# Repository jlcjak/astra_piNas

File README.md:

# Astra piNas — CM5 dual NVMe carrier

This project was an experiment in using GPT-6 Astra to create a complete PCB from a single initial prompt, followed by a request to fully route it.

**Initial prompt** *(lightly edited for spelling and grammar)*

> I need a new KiCad project with schematics for a small Raspberry Pi CM5 carrier board. It needs to take two full-size M.2 SSDs, so you will need a PCIe switch. Find parts for everything, along with symbols and footprints.
>
> It also needs one RJ45 Ethernet connector, an SD card slot, a barrel jack that accepts 9–25 V, PoE capability, and a power-only USB-C port. A second USB-C port should be used just for USB-to-UART.
>
> Find good symbols and footprints for everything, and keep it nice. Pay particular attention to the CM5 footprint and make sure it is correct. You have TI_API_KEY, TI_API_SECRET, MOUSER_API_KEY, DIGIKEY_CLIENT_ID and DIGIKEY_CLIENT_SECRET set as environment variables in `~/.local/share/codex`. You also have easyeda2kicad installed. You can use the other APIs for datasheets and create your own footprints too.
>
> Remember to put the footprints and symbols in self-contained project libraries. All parts should be well in stock and have a MANUFACTURER PART NUMBER property. Actually, let's use only in-stock LCSC parts, with 0402 as the minimum component size. Try to minimize the component count and number of passives.
>
> Place things logically on the board afterward so it is easy for me to route. Explicitly: do not look for other work on this computer that might help. It will not help and must not be used. Strictly.

**Routing follow-up** *(lightly edited for spelling and grammar)*

> OK, now fully route it. Feel free to move things around as much as you like; I like the current size. Make it nice and clean, and pick the stackup and everything. Use six layers at most. I think six makes sense here, actually.

Open **[astra_piNas.kicad_pro](astra_piNas.kicad_pro)** in **KiCad 10**. The project contains nine schematic sheets and a fully routed **100 × 120 mm, six-layer** board. Both 2280 NVMe sockets are on the underside. Use a **CM5 Lite** for the native microSD interface.

- [Routing and placement notes](docs/ROUTING.md), [selected stackup](docs/STACKUP.md)
- [Schematic PDF](docs/schematics.pdf)
- [Top copper view](docs/routing_top.svg), [bottom copper view](docs/routing_bottom.svg)
- [Top assembly view](docs/placement_top.svg), [bottom assembly view](docs/placement_bottom.svg)
- [BOM with MPNs and LCSC stock snapshots](docs/BOM.csv), [library provenance](docs/LIBRARIES.md)
- [Final validation summary](docs/routing_validation.json), [pair measurements](docs/pair_lengths.csv)
- [ERC](docs/erc.rpt), [PCB DRC](docs/drc.rpt), [schematic parity](docs/schematic_parity.rpt)

All symbols and footprints resolve through the project-local library tables to `lib/`. Available 3D models use project-relative paths. No unrelated local project was searched or reused; the Raspberry Pi reference files were downloaded from the official archive linked in [library provenance](docs/LIBRARIES.md).

The main project files above are the current design. Local routing experiments, tool caches and the downloaded CM5IO reference archive are excluded from this repository. Final routing measurements and validation reports are included under `docs/`. Regeneration scripts can overwrite manual edits. No fabrication package is released while the PoE hold remains unresolved.

**Board views**

Slightly angled 3D views of both sides, with project-local passive models:

Top and bottom placement views:

| Top | Bottom |
| --- | --- |
|  |  |

All six copper layers, viewed from the top in stackup order:

Individual layers are shown below. Click a layer name for the full-resolution vector drawing.

| Layer | Copper view |
| --- | --- |
| [L1 · F.Cu — outer routing](docs/images/astra_piNas-F_Cu.svg) |  |
| [L2 · In1.Cu — ground reference](docs/images/astra_piNas-In1_Cu.svg) |  |
| [L3 · In2.Cu — power and slow signals](docs/images/astra_piNas-In2_Cu.svg) |  |
| [L4 · In3.Cu — power and slow signals](docs/images/astra_piNas-In3_Cu.svg) |  |
| [L5 · In4.Cu — ground reference](docs/images/astra_piNas-In4_Cu.svg) |  |
| [L6 · B.Cu — outer routing](docs/images/astra_piNas-B_Cu.svg) |  |

**Schematic overview**

All nine sheets are shown below. Open the [schematic PDF](docs/schematics.pdf) to zoom into individual circuits.

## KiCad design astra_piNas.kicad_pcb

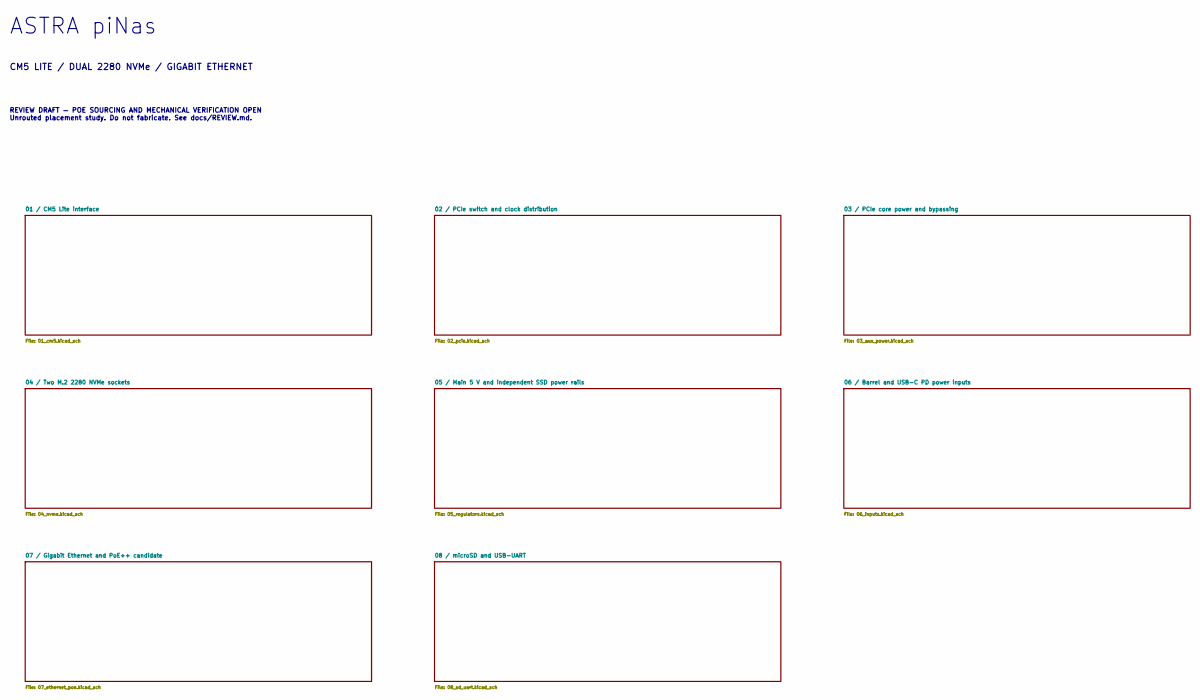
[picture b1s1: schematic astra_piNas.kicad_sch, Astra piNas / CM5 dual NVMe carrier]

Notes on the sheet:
ASTRA piNas
CM5 LITE / DUAL 2280 NVMe / GIGABIT ETHERNET
REVIEW DRAFT — POE SOURCING AND MECHANICAL VERIFICATION OPEN Unrouted placement study. Do not fabricate. See docs/REVIEW.md.

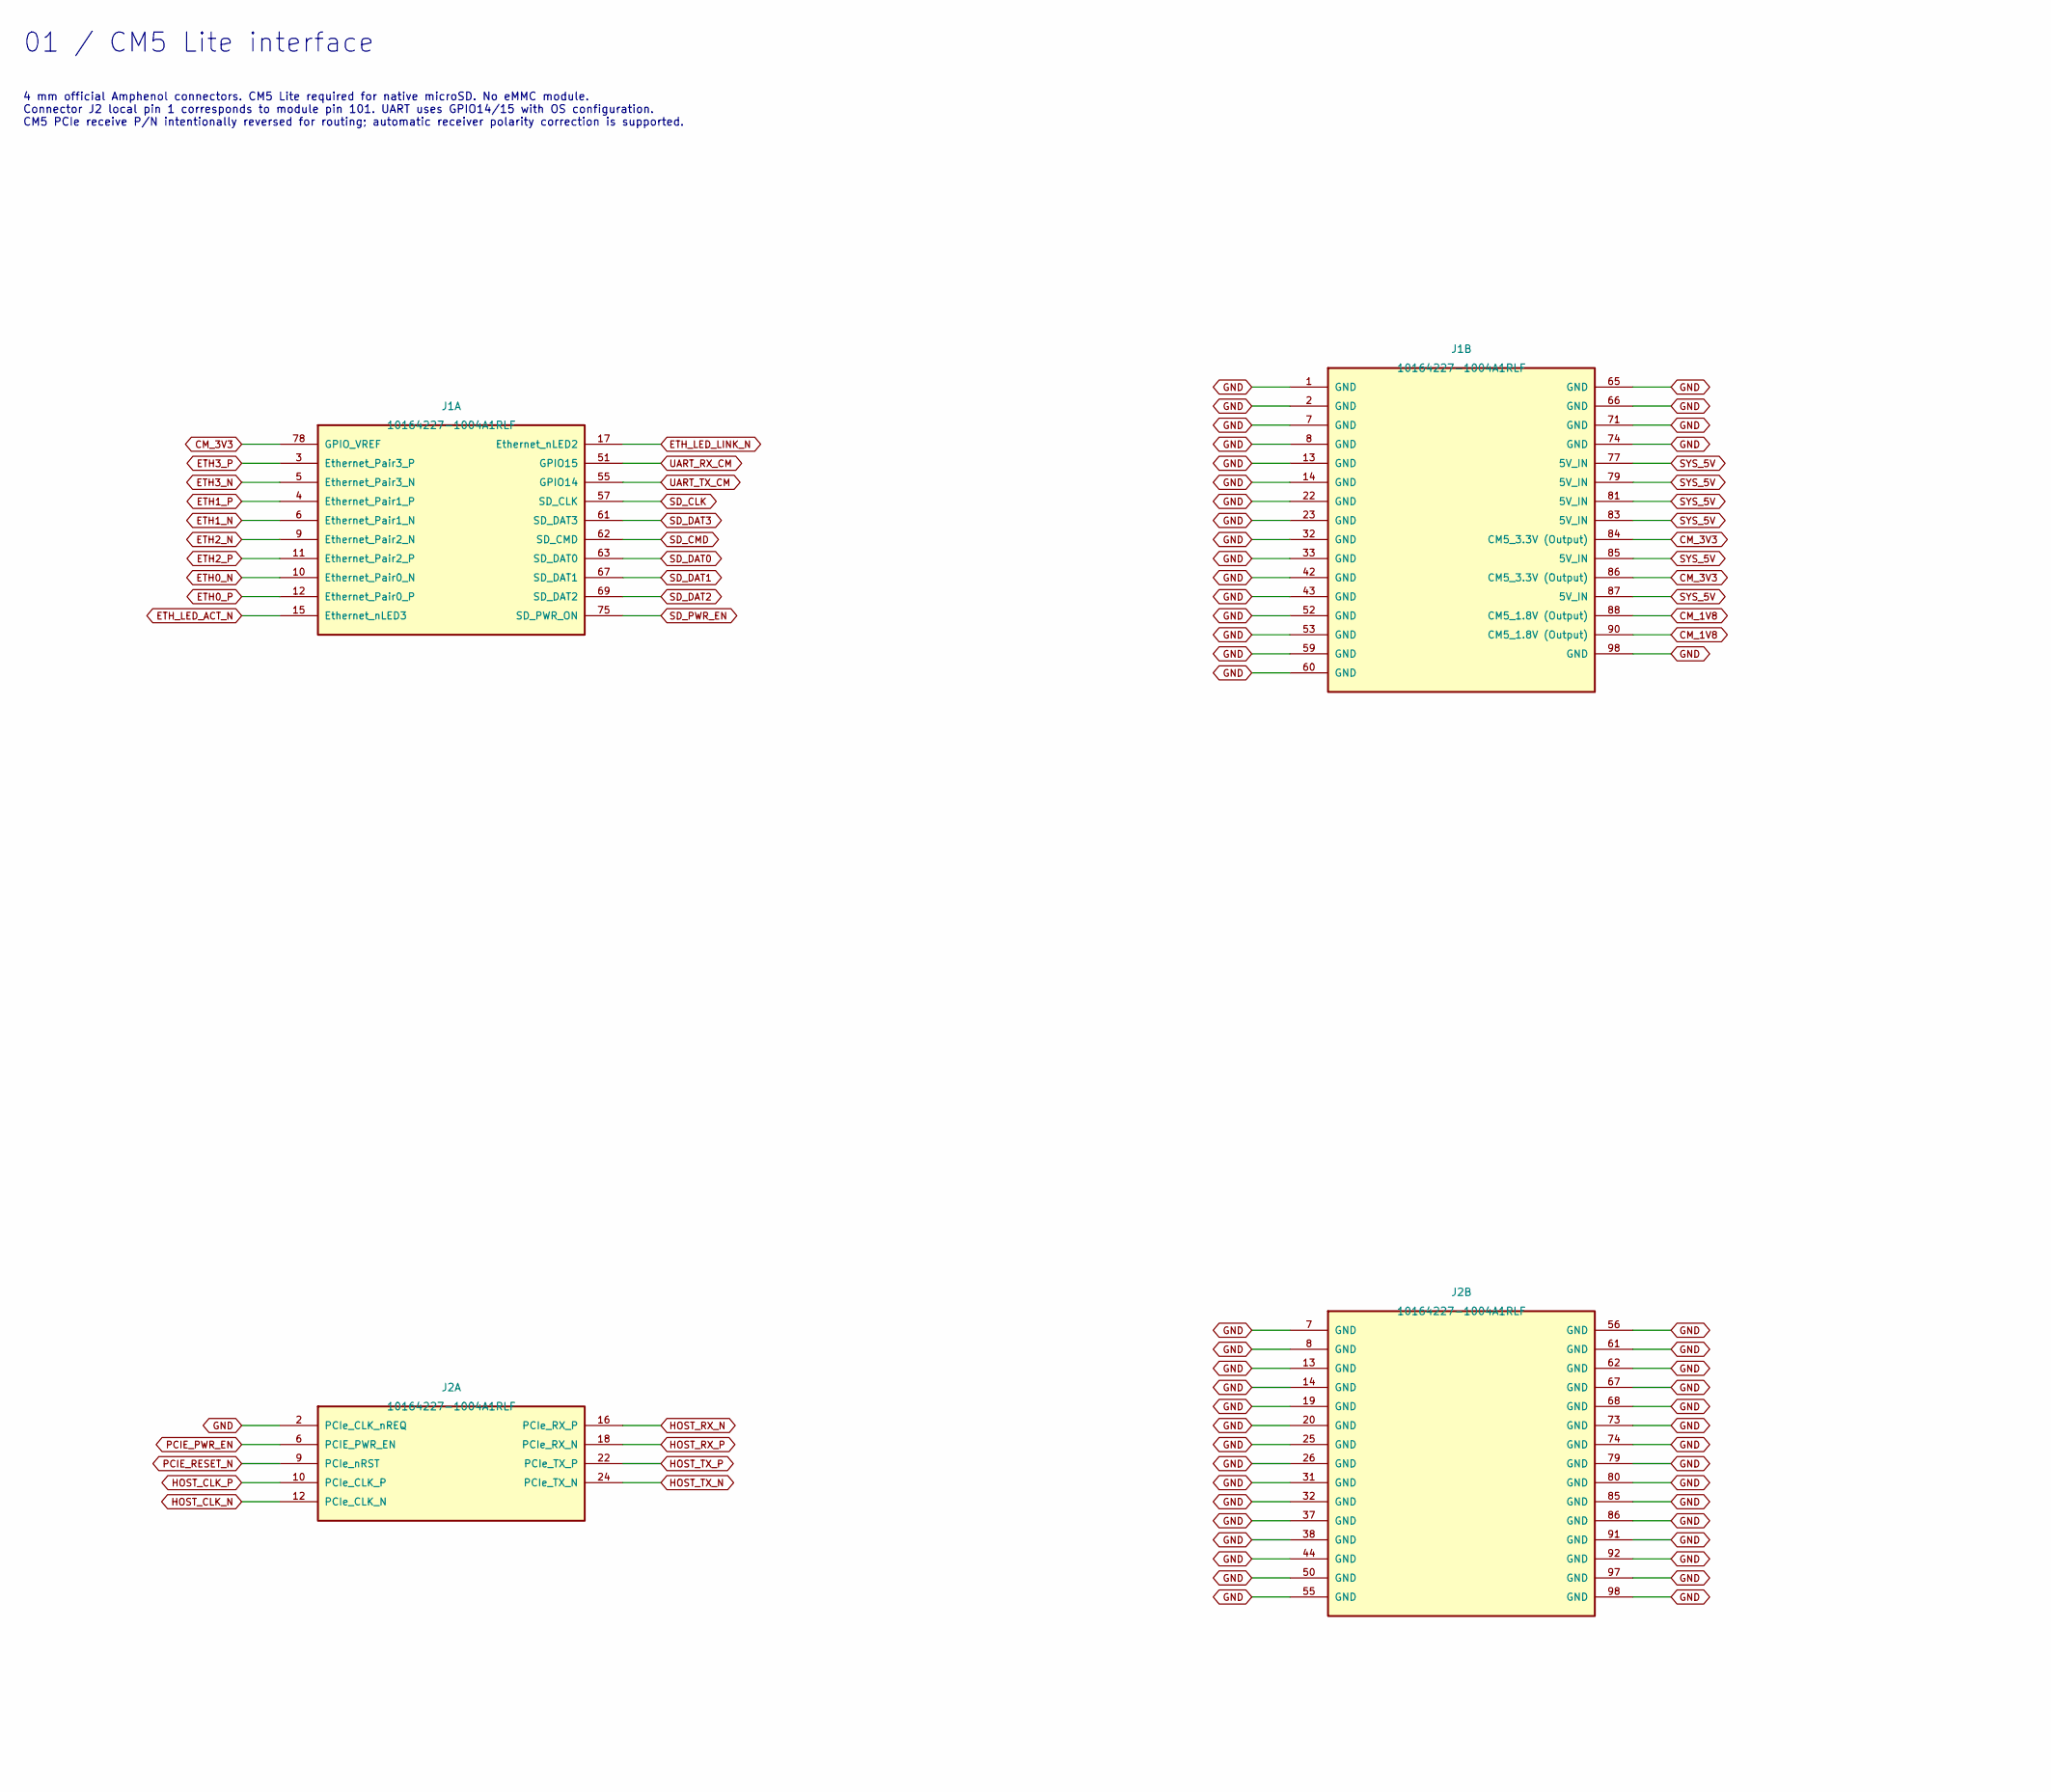
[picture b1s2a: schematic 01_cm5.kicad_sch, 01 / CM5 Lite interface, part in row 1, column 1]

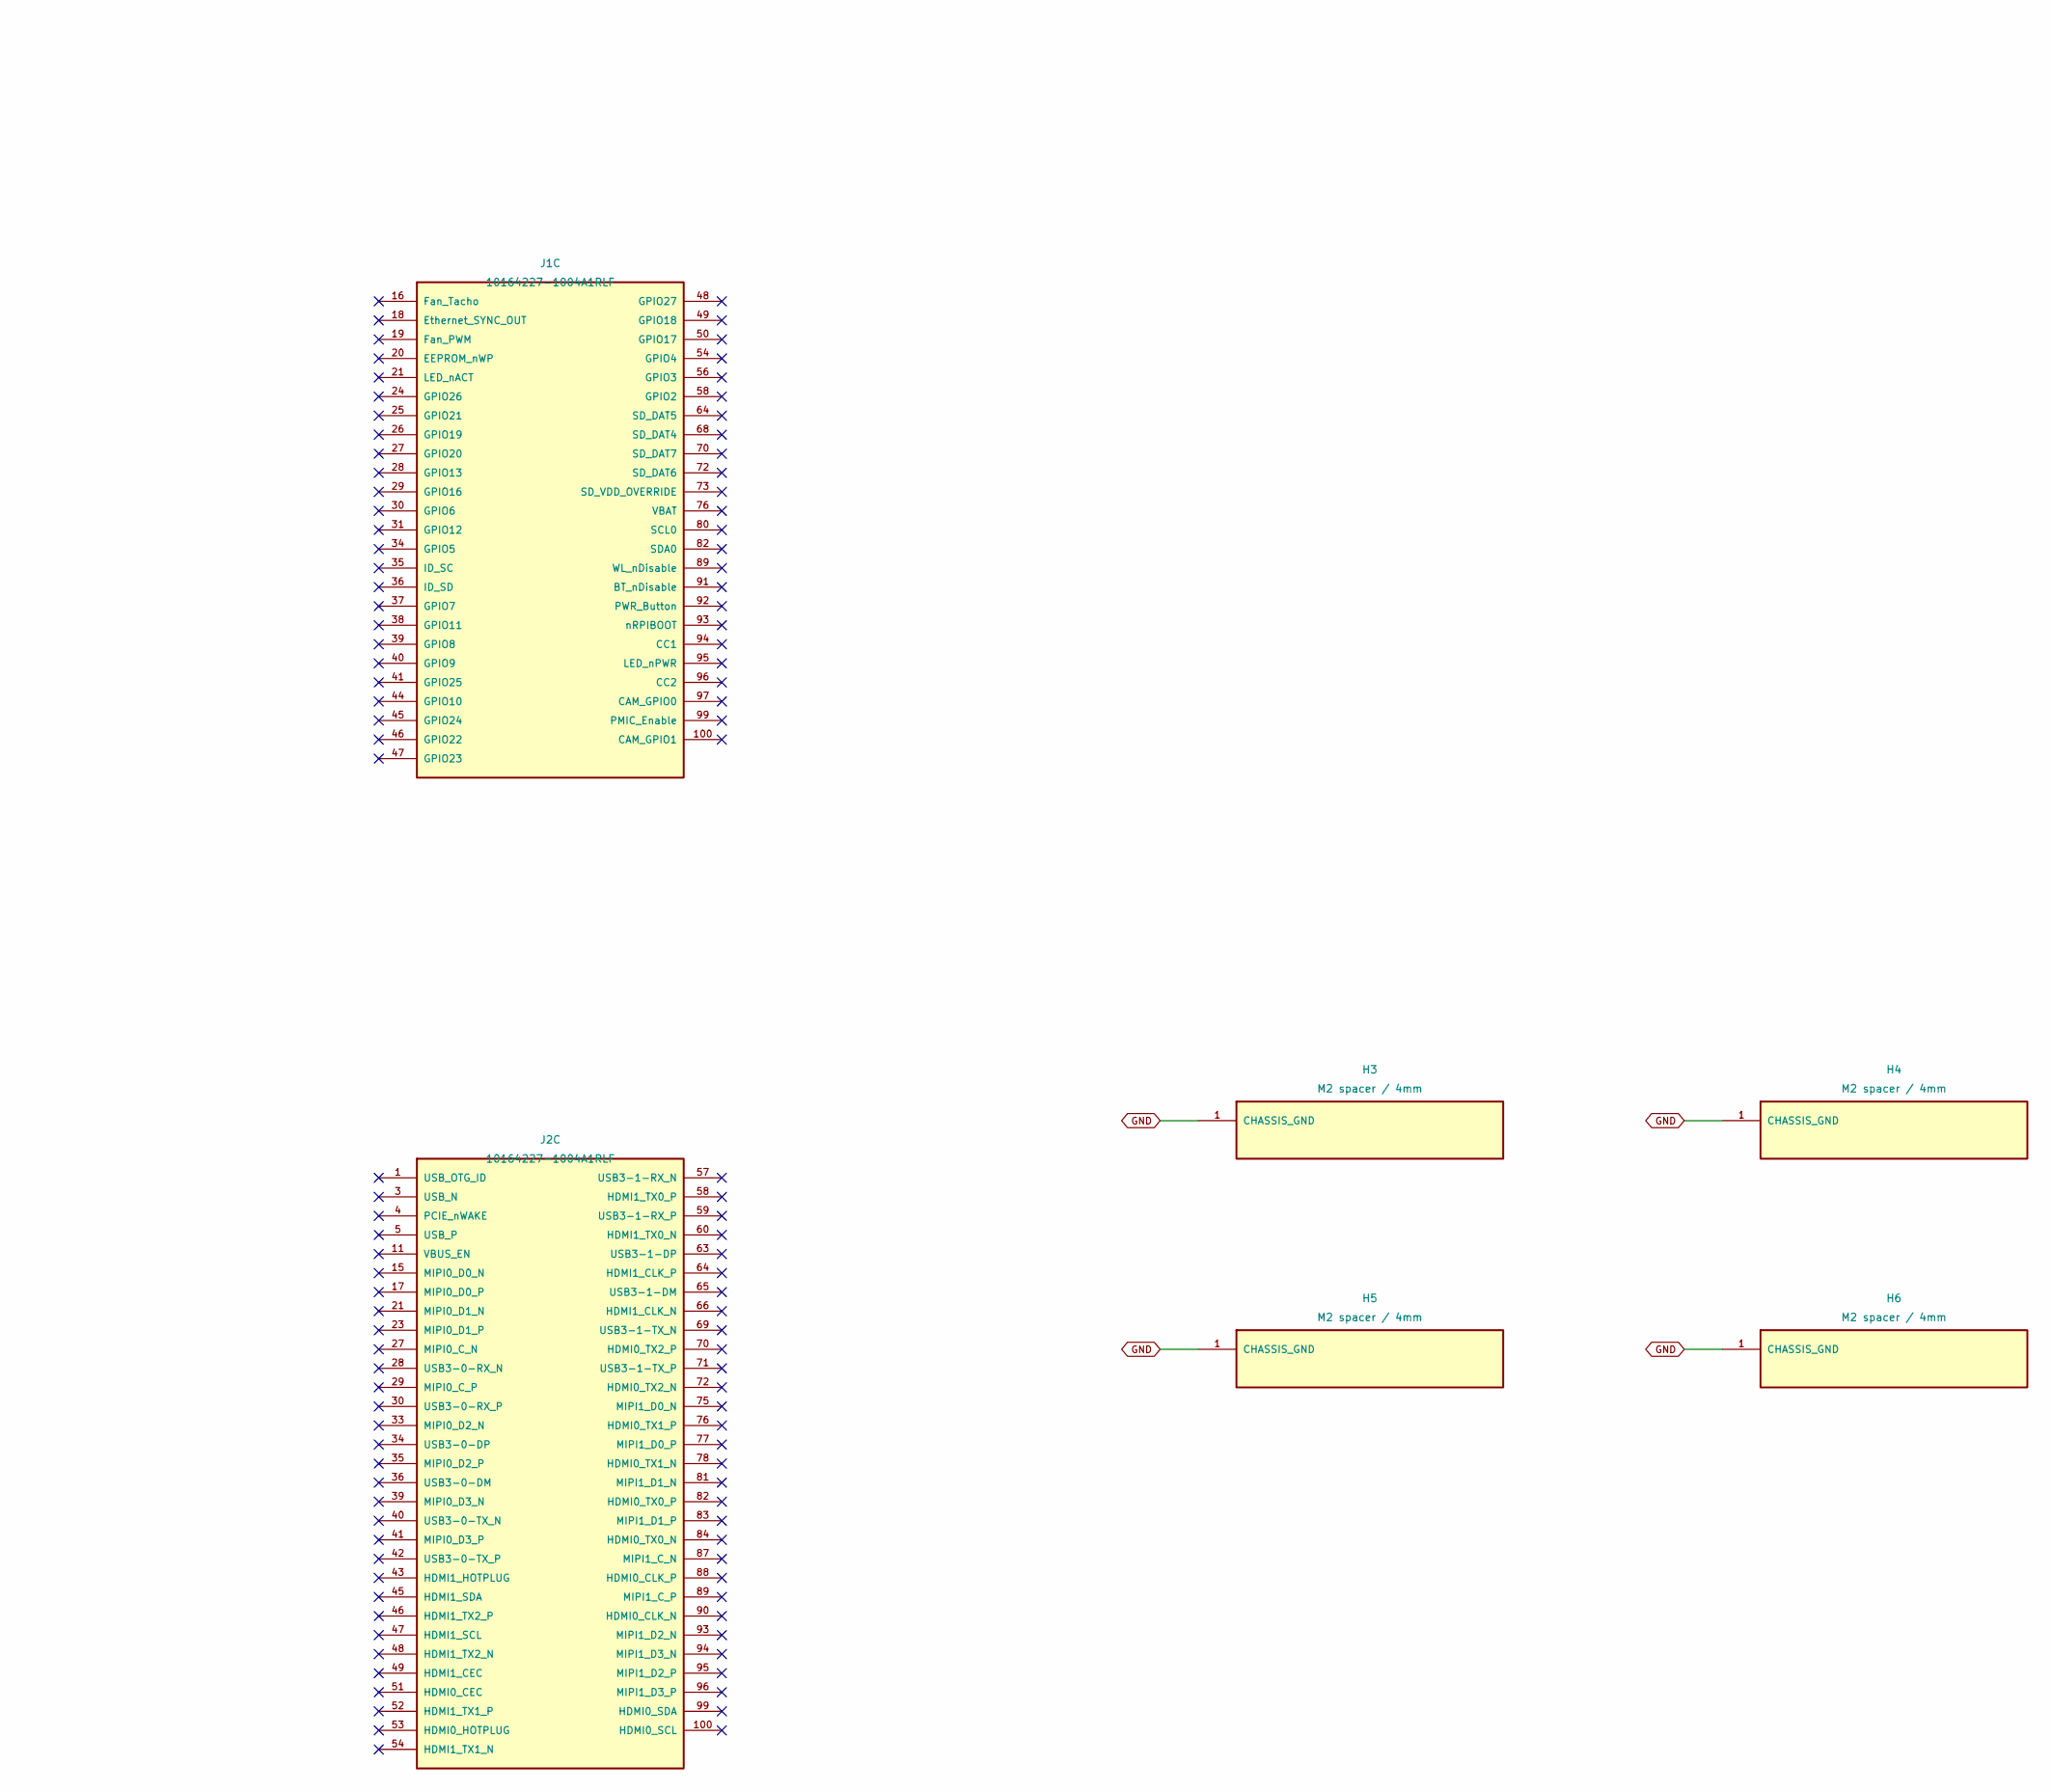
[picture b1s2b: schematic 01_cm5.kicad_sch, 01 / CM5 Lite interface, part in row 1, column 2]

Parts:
H3, H4, H5, H6: M2 spacer / 4mm; YIYUAN_SMTSOM240BTR; MANUFACTURER PART NUMBER SMTSOM240BTR; LCSC Part Number C19626599
J1, J2: 10164227-1004A1RLF; CM5_Amphenol_10164227_1004_OfficialPads; MANUFACTURER PART NUMBER 10164227-1004A1RLF; LCSC Part Number C7435219

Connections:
CM_1V8: J1.88 (CM5_1.8V (Output)), J1.90 (CM5_1.8V (Output))
CM_3V3: J1.78 (GPIO_VREF), J1.84 (CM5_3.3V (Output)), J1.86 (CM5_3.3V (Output)); also elsewhere on the board
ETH0_N: J1.10 (Ethernet_Pair0_N); also elsewhere on the board
ETH0_P: J1.12 (Ethernet_Pair0_P); also elsewhere on the board
ETH1_N: J1.6 (Ethernet_Pair1_N); also elsewhere on the board
ETH1_P: J1.4 (Ethernet_Pair1_P); also elsewhere on the board
ETH2_N: J1.9 (Ethernet_Pair2_N); also elsewhere on the board
ETH2_P: J1.11 (Ethernet_Pair2_P); also elsewhere on the board
ETH3_N: J1.5 (Ethernet_Pair3_N); also elsewhere on the board
ETH3_P: J1.3 (Ethernet_Pair3_P); also elsewhere on the board
ETH_LED_ACT_N: J1.15 (Ethernet_nLED3); also elsewhere on the board
ETH_LED_LINK_N: J1.17 (Ethernet_nLED2); also elsewhere on the board
GND: H3.1, H4.1, H5.1, H6.1, J1.1 (GND), J1.2 (GND), J1.7 (GND), J1.8 (GND), J1.13 (GND), J1.14 (GND), J1.22 (GND), J1.23 (GND), J1.32 (GND), J1.33 (GND), J1.42 (GND), J1.43 (GND), J1.52 (GND), J1.53 (GND), J1.59 (GND), J1.60 (GND), J1.65 (GND), J1.66 (GND), J1.71 (GND), J1.74 (GND), J1.98 (GND), J2.2 (PCIe_CLK_nREQ), J2.7 (GND), J2.8 (GND), J2.13 (GND), J2.14 (GND), J2.19 (GND), J2.20 (GND), J2.25 (GND), J2.26 (GND), J2.31 (GND), J2.32 (GND), J2.37 (GND), J2.38 (GND), J2.44 (GND), J2.50 (GND), J2.55 (GND), J2.56 (GND), J2.61 (GND), J2.62 (GND), J2.67 (GND), J2.68 (GND), J2.73 (GND), J2.74 (GND), J2.79 (GND), J2.80 (GND), J2.85 (GND), J2.86 (GND), J2.91 (GND), J2.92 (GND), J2.97 (GND), J2.98 (GND); also elsewhere on the board
HOST_CLK_N: J2.12 (PCIe_CLK_N); also elsewhere on the board
HOST_CLK_P: J2.10 (PCIe_CLK_P); also elsewhere on the board
HOST_RX_N: J2.16 (PCIe_RX_P); also elsewhere on the board
HOST_RX_P: J2.18 (PCIe_RX_N); also elsewhere on the board
HOST_TX_N: J2.24 (PCIe_TX_N); also elsewhere on the board
HOST_TX_P: J2.22 (PCIe_TX_P); also elsewhere on the board
PCIE_PWR_EN: J2.6 (PCIE_PWR_EN); also elsewhere on the board
PCIE_RESET_N: J2.9 (PCIe_nRST); also elsewhere on the board
SD_CLK: J1.57 (SD_CLK); also elsewhere on the board
SD_CMD: J1.62 (SD_CMD); also elsewhere on the board
SD_DAT0: J1.63 (SD_DAT0); also elsewhere on the board
SD_DAT1: J1.67 (SD_DAT1); also elsewhere on the board
SD_DAT2: J1.69 (SD_DAT2); also elsewhere on the board
SD_DAT3: J1.61 (SD_DAT3); also elsewhere on the board
SD_PWR_EN: J1.75 (SD_PWR_ON); also elsewhere on the board
SYS_5V: J1.77 (5V_IN), J1.79 (5V_IN), J1.81 (5V_IN), J1.83 (5V_IN), J1.85 (5V_IN), J1.87 (5V_IN); also elsewhere on the board
UART_RX_CM: J1.51 (GPIO15); also elsewhere on the board
UART_TX_CM: J1.55 (GPIO14); also elsewhere on the board

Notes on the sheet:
01 / CM5 Lite interface
4 mm official Amphenol connectors. CM5 Lite required for native microSD. No eMMC module. Connector J2 local pin 1 corresponds to module pin 101. UART uses GPIO14/15 with OS configuration. CM5 PCIe receive P/N intentionally reversed for routing; automatic receiver polarity correction is supported.

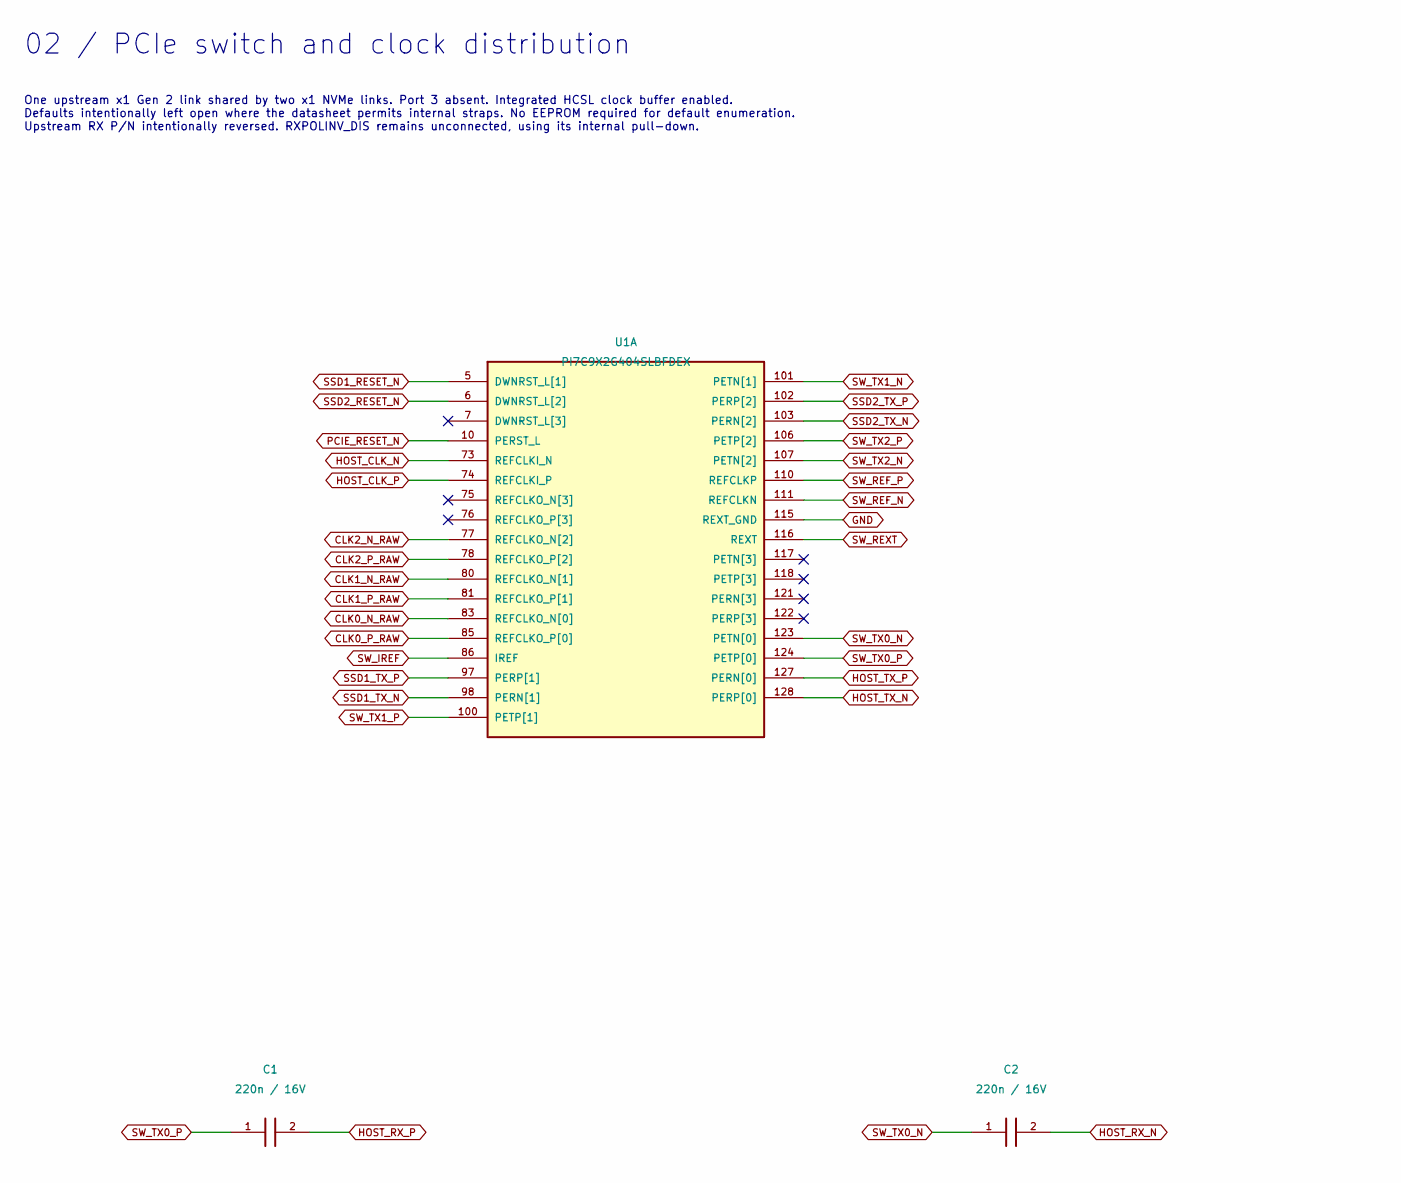
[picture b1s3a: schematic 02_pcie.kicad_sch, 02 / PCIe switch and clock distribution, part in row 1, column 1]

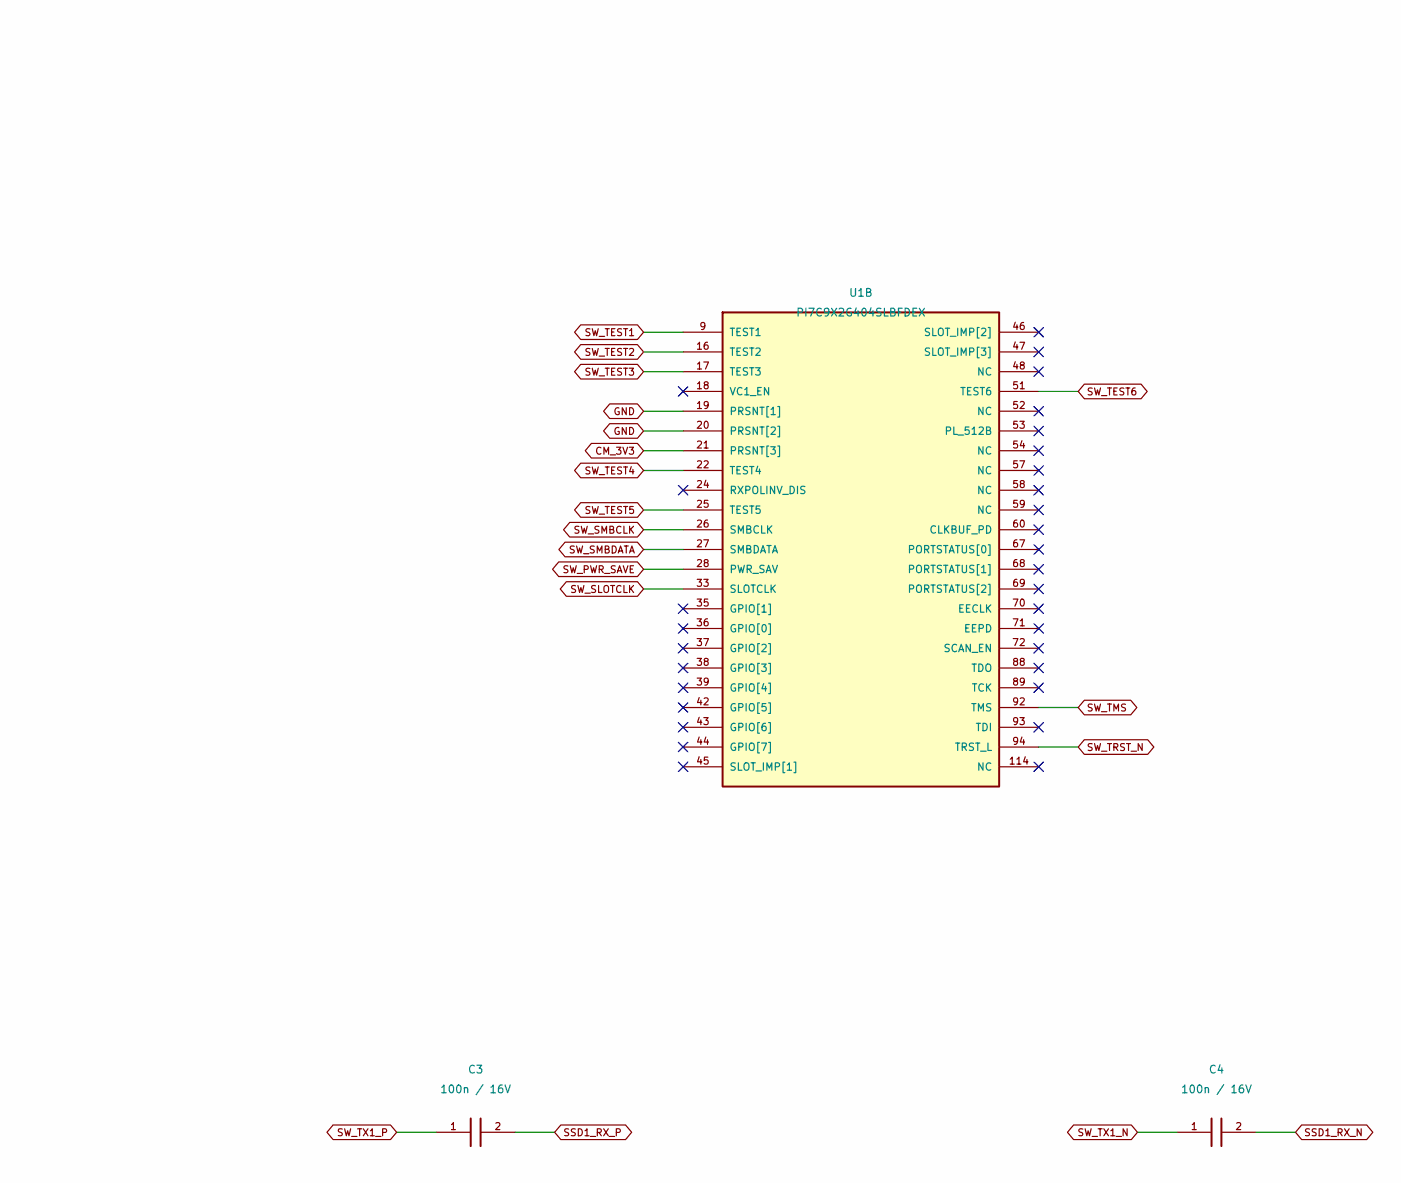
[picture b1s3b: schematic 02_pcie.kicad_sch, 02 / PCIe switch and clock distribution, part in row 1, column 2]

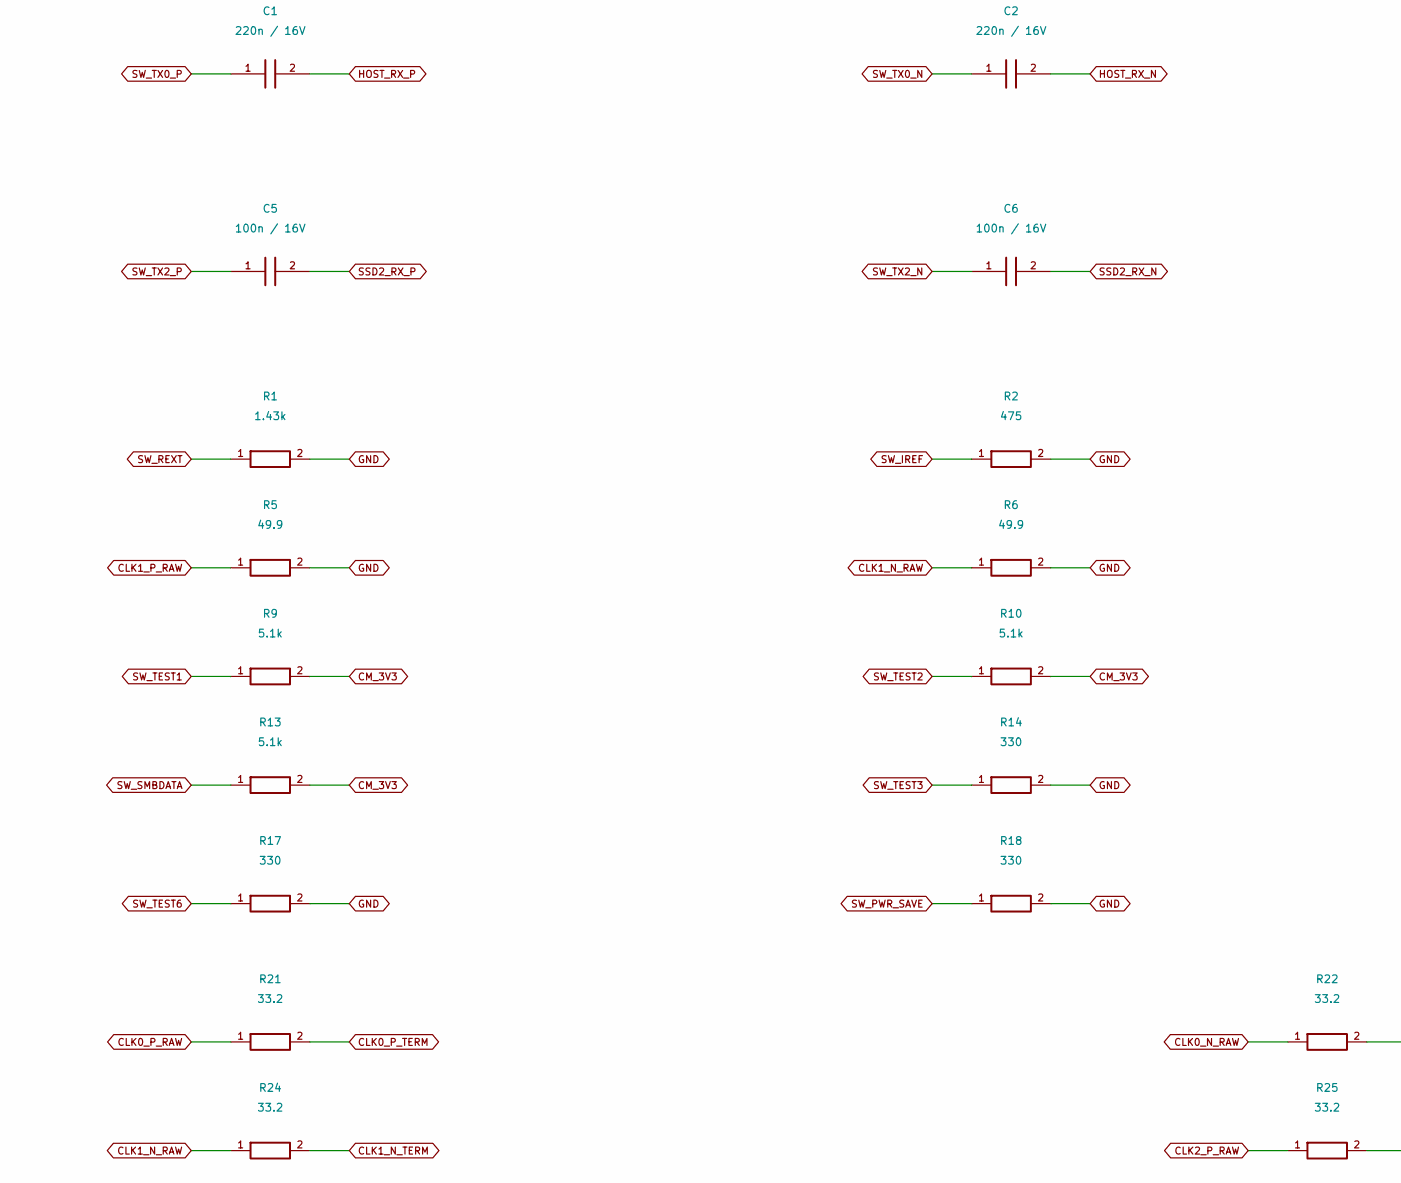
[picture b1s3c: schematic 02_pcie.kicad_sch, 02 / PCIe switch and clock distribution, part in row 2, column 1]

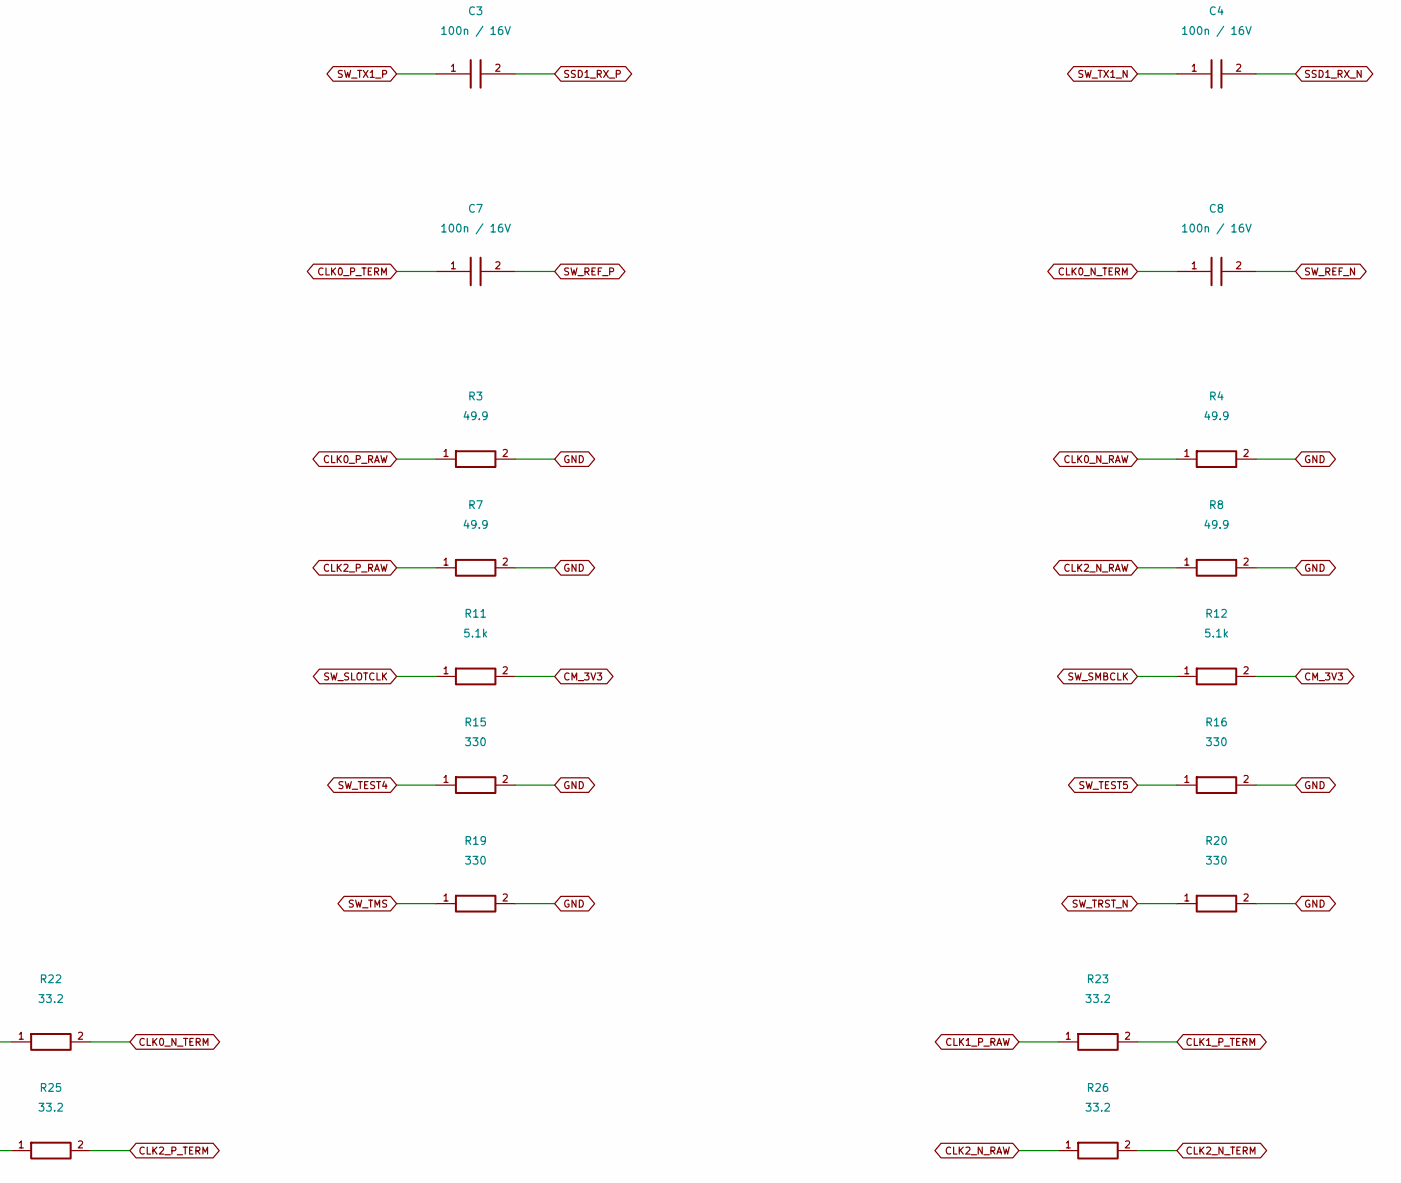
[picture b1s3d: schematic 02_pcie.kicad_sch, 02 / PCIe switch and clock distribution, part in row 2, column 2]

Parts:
C1, C2: 220n / 16V; C_0402_1005Metric; MANUFACTURER PART NUMBER CL05B224KO5NNNC; LCSC Part Number C16772
C3, C4, C5, C6, C7, C8: 100n / 16V; C_0402_1005Metric; MANUFACTURER PART NUMBER CL05B104KO5NNNC; LCSC Part Number C1525
R1: 1.43k; R_0603_1608Metric; MANUFACTURER PART NUMBER 0603WAF1431T5E; LCSC Part Number C22840
R2: 475; R_0603_1608Metric; MANUFACTURER PART NUMBER 0603WAF4750T5E; LCSC Part Number C23181
R3, R4, R5, R6, R7, R8: 49.9; R_0402_1005Metric; MANUFACTURER PART NUMBER 0402WGF499JTCE; LCSC Part Number C25120
R9, R10, R11, R12, R13: 5.1k; R_0603_1608Metric; MANUFACTURER PART NUMBER 0603WAF5101T5E; LCSC Part Number C23186
R14, R15, R16, R17, R18, R19, R20: 330; R_0603_1608Metric; MANUFACTURER PART NUMBER 0603WAF3300T5E; LCSC Part Number C23138
R21, R22, R23, R24, R25, R26: 33.2; R_0402_1005Metric; MANUFACTURER PART NUMBER 0402WGF332JTCE; LCSC Part Number C25106
U1: PI7C9X2G404SLBFDEX; LQFP-128_L14.0-W14.0-P0.40-LS16.0-BL-EP5.8; MANUFACTURER PART NUMBER PI7C9X2G404SLBFDEX; LCSC Part Number C500767

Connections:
CLK0_N_RAW: R4.1, R22.1, U1.83 (REFCLKO_N[0])
CLK0_N_TERM: C8.1, R22.2
CLK0_P_RAW: R3.1, R21.1, U1.85 (REFCLKO_P[0])
CLK0_P_TERM: C7.1, R21.2
CLK1_N_RAW: R6.1, R24.1, U1.80 (REFCLKO_N[1])
CLK1_N_TERM: R24.2; also elsewhere on the board
CLK1_P_RAW: R5.1, R23.1, U1.81 (REFCLKO_P[1])
CLK1_P_TERM: R23.2; also elsewhere on the board
CLK2_N_RAW: R8.1, R26.1, U1.77 (REFCLKO_N[2])
CLK2_N_TERM: R26.2; also elsewhere on the board
CLK2_P_RAW: R7.1, R25.1, U1.78 (REFCLKO_P[2])
CLK2_P_TERM: R25.2; also elsewhere on the board
CM_3V3: R9.2, R10.2, R11.2, R12.2, R13.2, U1.21 (PRSNT[3]); also elsewhere on the board
GND: R1.2, R2.2, R3.2, R4.2, R5.2, R6.2, R7.2, R8.2, R14.2, R15.2, R16.2, R17.2, R18.2, R19.2, R20.2, U1.19 (PRSNT[1]), U1.20 (PRSNT[2]), U1.115 (REXT_GND); also elsewhere on the board
HOST_CLK_N: U1.73 (REFCLKI_N); also elsewhere on the board
HOST_CLK_P: U1.74 (REFCLKI_P); also elsewhere on the board
HOST_RX_N: C2.2; also elsewhere on the board
HOST_RX_P: C1.2; also elsewhere on the board
HOST_TX_N: U1.128 (PERP[0]); also elsewhere on the board
HOST_TX_P: U1.127 (PERN[0]); also elsewhere on the board
PCIE_RESET_N: U1.10 (PERST_L); also elsewhere on the board
SSD1_RESET_N: U1.5 (DWNRST_L[1]); also elsewhere on the board
SSD1_RX_N: C4.2; also elsewhere on the board
SSD1_RX_P: C3.2; also elsewhere on the board
SSD1_TX_N: U1.98 (PERN[1]); also elsewhere on the board
SSD1_TX_P: U1.97 (PERP[1]); also elsewhere on the board
SSD2_RESET_N: U1.6 (DWNRST_L[2]); also elsewhere on the board
SSD2_RX_N: C6.2; also elsewhere on the board
SSD2_RX_P: C5.2; also elsewhere on the board
SSD2_TX_N: U1.103 (PERN[2]); also elsewhere on the board
SSD2_TX_P: U1.102 (PERP[2]); also elsewhere on the board
SW_IREF: R2.1, U1.86 (IREF)
SW_PWR_SAVE: R18.1, U1.28 (PWR_SAV)
SW_REF_N: C8.2, U1.111 (REFCLKN)
SW_REF_P: C7.2, U1.110 (REFCLKP)
SW_REXT: R1.1, U1.116 (REXT)
SW_SLOTCLK: R11.1, U1.33 (SLOTCLK)
SW_SMBCLK: R12.1, U1.26 (SMBCLK)
SW_SMBDATA: R13.1, U1.27 (SMBDATA)
SW_TEST1: R9.1, U1.9 (TEST1)
SW_TEST2: R10.1, U1.16 (TEST2)
SW_TEST3: R14.1, U1.17 (TEST3)
SW_TEST4: R15.1, U1.22 (TEST4)
SW_TEST5: R16.1, U1.25 (TEST5)
SW_TEST6: R17.1, U1.51 (TEST6)
SW_TMS: R19.1, U1.92 (TMS)
SW_TRST_N: R20.1, U1.94 (TRST_L)
SW_TX0_N: C2.1, U1.123 (PETN[0])
SW_TX0_P: C1.1, U1.124 (PETP[0])
SW_TX1_N: C4.1, U1.101 (PETN[1])
SW_TX1_P: C3.1, U1.100 (PETP[1])
SW_TX2_N: C6.1, U1.107 (PETN[2])
SW_TX2_P: C5.1, U1.106 (PETP[2])

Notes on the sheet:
02 / PCIe switch and clock distribution
One upstream x1 Gen 2 link shared by two x1 NVMe links. Port 3 absent. Integrated HCSL clock buffer enabled. Defaults intentionally left open where the datasheet permits internal straps. No EEPROM required for default enumeration. Upstream RX P/N intentionally reversed. RXPOLINV_DIS remains unconne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
